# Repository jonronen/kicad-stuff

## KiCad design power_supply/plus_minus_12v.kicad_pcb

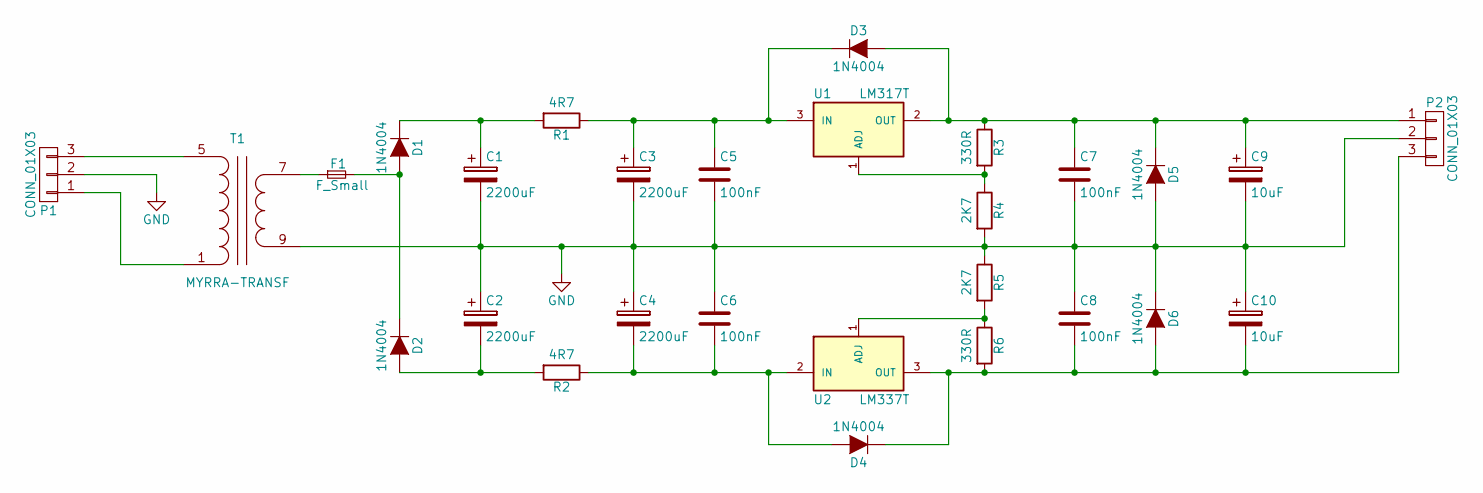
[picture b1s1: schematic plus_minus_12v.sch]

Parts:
C1, C2, C3, C4: 2200uF; C_Radial_D16_L30_P7.5
C5, C6, C7, C8: 100nF; C_Rect_L4_W2.5_P2.5
C9, C10: 10uF; C_Radial_D5_L11_P2
D1, D2, D3, D4, D5, D6: 1N4004; DO-35
F1: F_Small; C_Disc_D6_P5
P1: CONN_01X03; TerminalBlock_Pheonix_MKDS1.5-3pol
P2: CONN_01X03; Socket_MOLEX-KK-RM2-54mm_Lock_3pin_straight
R1, R2: 4R7; Resistor_SMD+THTuniversal_2512_RM10_HandSoldering
R3, R6: 330R; Resistor_SMD+THTuniversal_0805to1206_RM10_HandSoldering
R4, R5: 2K7; Resistor_SMD+THTuniversal_0805to1206_RM10_HandSoldering
T1: MYRRA-TRANSF; Trafo_CHK-EI42-5VA_1xSec
U1: LM317T; TO-220_Neutral123_Vertical
U2: LM337T; TO-220_Neutral123_Vertical

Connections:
GND: C1.2, C2.1, C3.2, C4.1, C5.2, C6.1, C7.2, C8.1, C9.2, C10.1, D5.2 (A), D6.1 (K), P1.2, P2.2, R4.2, R5.1, T1.9 (SA)
unnamed: C1.1, D1.1 (K), R1.2
unnamed: C2.2, D2.2 (A), R2.2
unnamed: C3.1, C5.1, D3.1 (K), R1.1, U1.3 (IN)
unnamed: C4.2, C6.2, D4.2 (A), R2.1, U2.2 (IN)
unnamed: C7.1, C9.1, D3.2 (A), D5.1 (K), P2.1, R3.1, U1.2 (OUT)
unnamed: C8.2, C10.2, D4.1 (K), D6.2 (A), P2.3, R6.2, U2.3 (OUT)
unnamed: D1.2 (A), D2.1 (K), F1.2
unnamed: F1.1, T1.7 (SB)
unnamed: P1.1, T1.1 (AB)
unnamed: P1.3, T1.5 (AA)
unnamed: R3.2, R4.1, U1.1 (ADJ)
unnamed: R5.2, R6.1, U2.1 (ADJ)

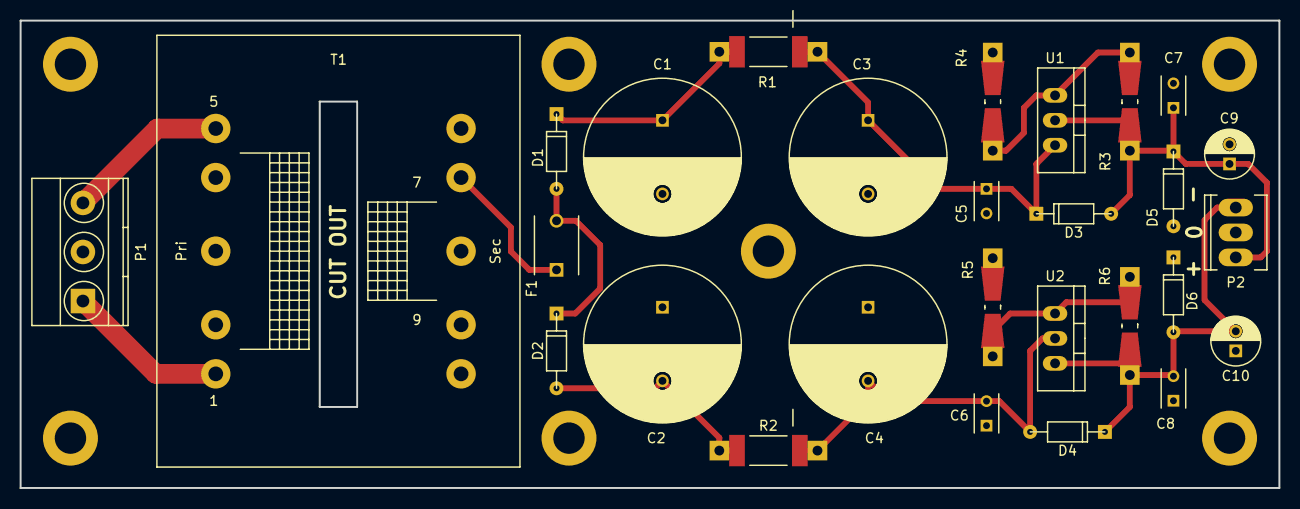
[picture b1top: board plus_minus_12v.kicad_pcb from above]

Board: 2 copper layers, 128.3 x 47.6 mm, 28 parts (0 on the bottom side), 13 nets.

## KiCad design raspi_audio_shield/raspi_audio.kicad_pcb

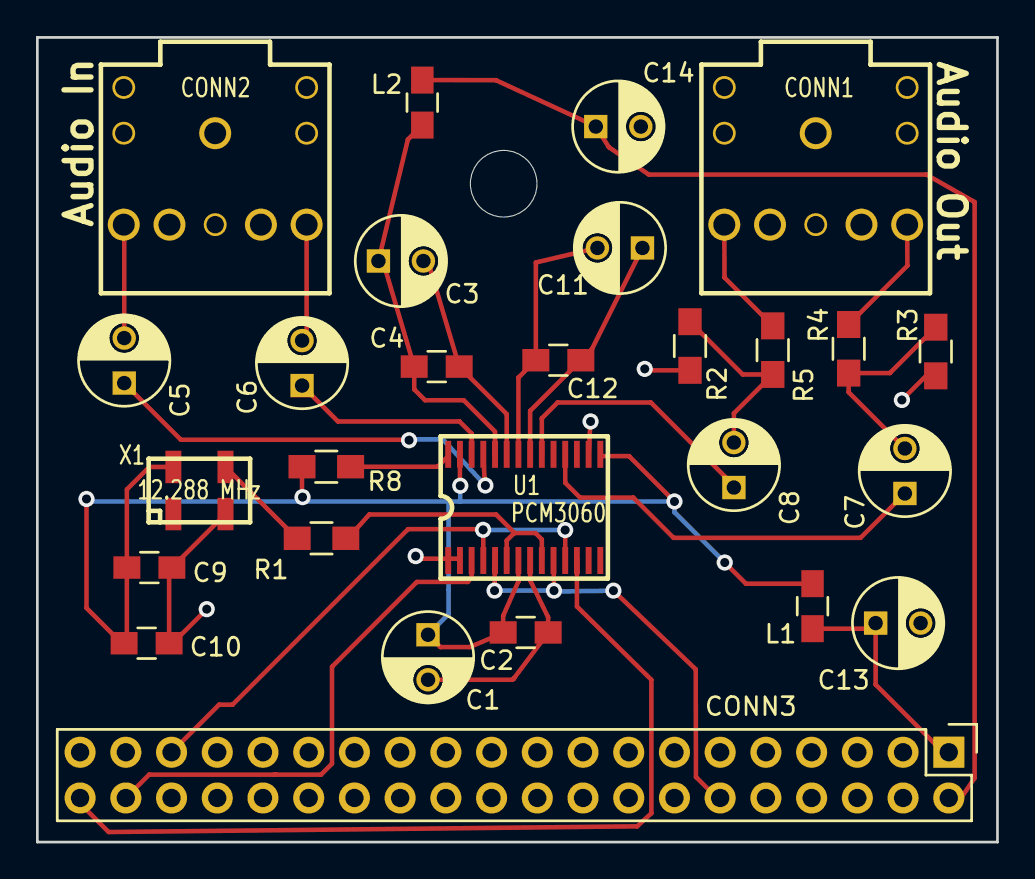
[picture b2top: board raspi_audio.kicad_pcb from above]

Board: 2 copper layers, 53.3 x 44.7 mm, 27 parts (0 on the bottom side), 23 nets.

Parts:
C1, C3, C11: 10uF; C_Radial_D5_L11_P2.5
C2, C4, C10, C12: 100nF; C_0805_HandSoldering
C5, C6: 4.7uF; C_Radial_D5_L11_P2.5
C7, C8: 22uF; C_Radial_D5_L11_P2.5
C9: 10nF; C_0805_HandSoldering
C13, C14: 100uF; C_Radial_D5_L11_P2.5
CONN1, CONN2: JACK_STEREO; AUDIO_STEREO_CONN
CONN3: CONN_02X20; Pin_Header_Straight_2x20
L1, L2: 2200Ohm,200mA; C_0805_HandSoldering
R1: 47R; R_0805_HandSoldering
R2, R3: 10K; R_0805_HandSoldering
R4, R5: 100R; R_0805_HandSoldering
R8: 220K; R_0805_HandSoldering
U1: PCM3060; GEDA_TSSOP28
X1: 12.288 MHz; SMTOSC

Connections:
BCK: CONN3.12, U1.5, U1.10
DATAI: CONN3.40, U1.12
DATAO: CONN3.38, U1.3
Earth: C1.2, C2.2, C3.2, C4.2, C9.2, C10.2, C11.2, C12.2, C13.2, C14.2, CONN1.1, CONN1.4, CONN1.5, CONN2.1, CONN2.4, CONN2.5, CONN3.39, R2.2, R3.1, U1.1, U1.2, U1.8, U1.16, U1.22, U1.23, X1.2
INL: C5.2, CONN2.2
INR: C6.2, CONN2.3
unnamed: C5.1, U1.25
unnamed: C6.1, U1.26
unnamed: C7.1, U1.18
unnamed: C7.2, R3.2, R4.1
unnamed: C8.1, U1.20
unnamed: C8.2, R2.1, R5.2
unnamed: C11.1, C12.1, U1.21
unnamed: C13.1, CONN3.1, L1.2
unnamed: C14.1, CONN3.2, L2.2
unnamed: R1.1, U1.6, U1.9
unnamed: R8.1, U1.28
OUTL: CONN1.2, R5.1
OUTR: CONN1.3, R4.2
SYSCLK: R1.2, X1.3
VCC: C3.1, C4.1, L2.1, U1.24
VDD: C1.1, C2.1, C9.1, C10.1, L1.1, R8.2, U1.7, U1.15, U1.27, X1.4
WS: CONN3.35, U1.4, U1.11

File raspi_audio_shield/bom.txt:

L1, L2: 2x Ferrite bead, 2.2Kohm@100MHz, 200mA, 1ohm, 0805 SMD
X1: 12.288MHz 3.3V oscillator, FXO-HC536R-12.288, 3.2x5mm SMD
U1: Stereo Audio Codec, TI PCM3060PW, TSSOP-28
R1: Resistor, 47ohm, 0805 SMD
R2, R3: 2x Resistor, 10Kohm, 0805 SMD
R4, R5: 2x Resistor, 100ohm, 0805 SMD
R8: Resistor, 220Kohm, 0805 SMD
C1, C3, C11: 3x Radial Electrolytic Capacitor, 10uF, 50V, 5x11mm
C2, C4, C10, C12: 4x Capacitor, 100nF, 50V, 0805 SMD
C5, C6: 2x Radial Electrolytic Capacitor, 4.7uF, 50V, 5x11mm
C7, C8: 2x Radial Electrolytic Capacitor, 22uF, 50V, 5x11mm
C9: Capacitor, 10nF, 50V, 0805 SMD
C13, C14: 2x Radial Electrolytic Capacitor, 100uF, 35V, 6x11mm
CONN1, CONN2: 2x Stereo Enclosed Socket Chassis Jack
    http://www.taydaelectronics.com/hardware/3-5mm-plugs-jacks/3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
CONN3: Stackable Header, 2.54mm, 2x20 Pins (solder with pins facing up)

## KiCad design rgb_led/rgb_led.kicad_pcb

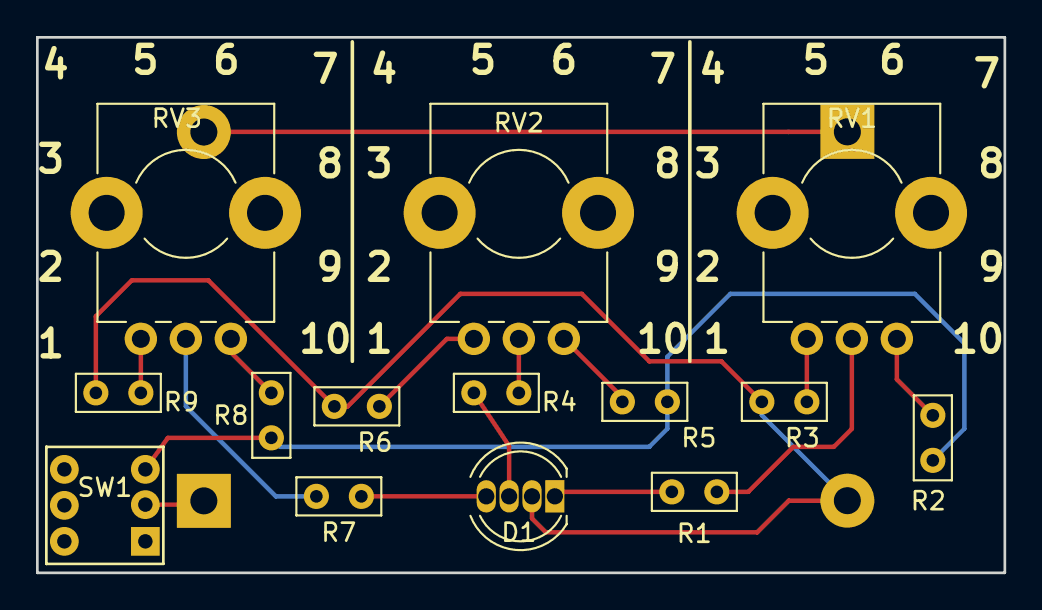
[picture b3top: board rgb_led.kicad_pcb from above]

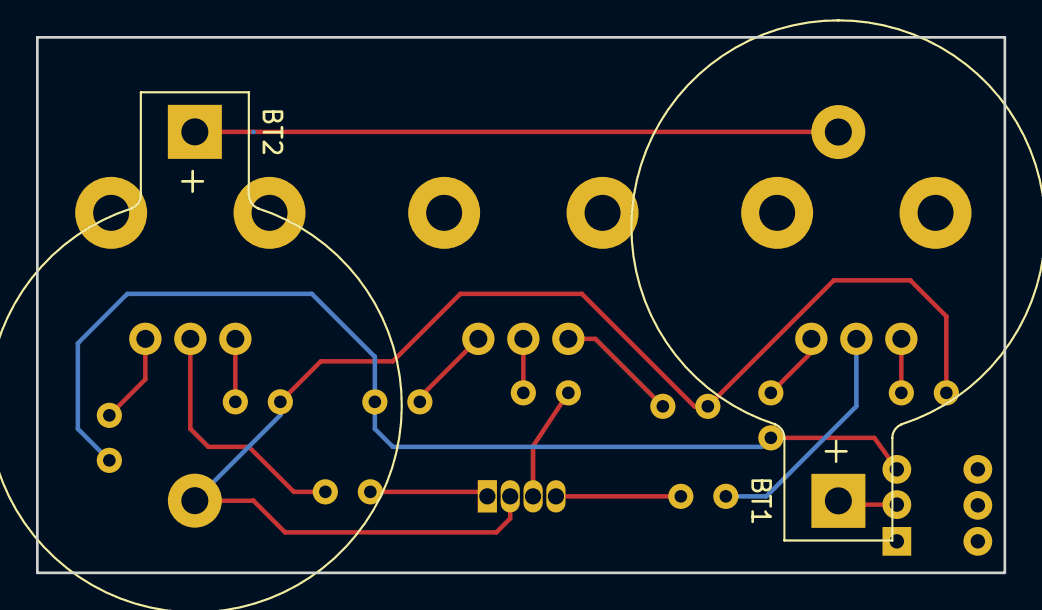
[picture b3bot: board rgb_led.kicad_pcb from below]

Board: 2 copper layers, 53.8 x 29.8 mm, 16 parts (2 on the bottom side), 16 nets.

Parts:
BT1, BT2: Battery_Cell; Keystone_103_1x20mm-CoinCell
D1: LED_RCGB; LED_D5.0mm-4
R1, R2, R3, R4, R5, R6, R7, R8, R9: R; C_Rect_L4.6mm_W2.0mm_P2.50mm_MKS02_FKP02
RV1, RV2, RV3: POT; Potentiometer_Bourns_PTV09A-1_Horizontal
SW1: SW_DPDT_x2; DPDT_6mm

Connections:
unnamed: BT1.1, SW1.2
unnamed: BT1.2, BT2.1
unnamed: BT2.2, D1.2, R3.2, R6.2, R9.2
unnamed: D1.1, R1.2
unnamed: D1.3, R4.2
unnamed: D1.4, R7.2
unnamed: R1.1, RV1.2
unnamed: R2.1, R5.1, R8.1, SW1.3
unnamed: R2.2, RV1.1
unnamed: R3.1, RV1.3
unnamed: R4.1, RV2.2
unnamed: R5.2, RV2.1
unnamed: R6.1, RV2.3
unnamed: R7.1, RV3.2
unnamed: R8.2, RV3.1
unnamed: R9.1, RV3.3

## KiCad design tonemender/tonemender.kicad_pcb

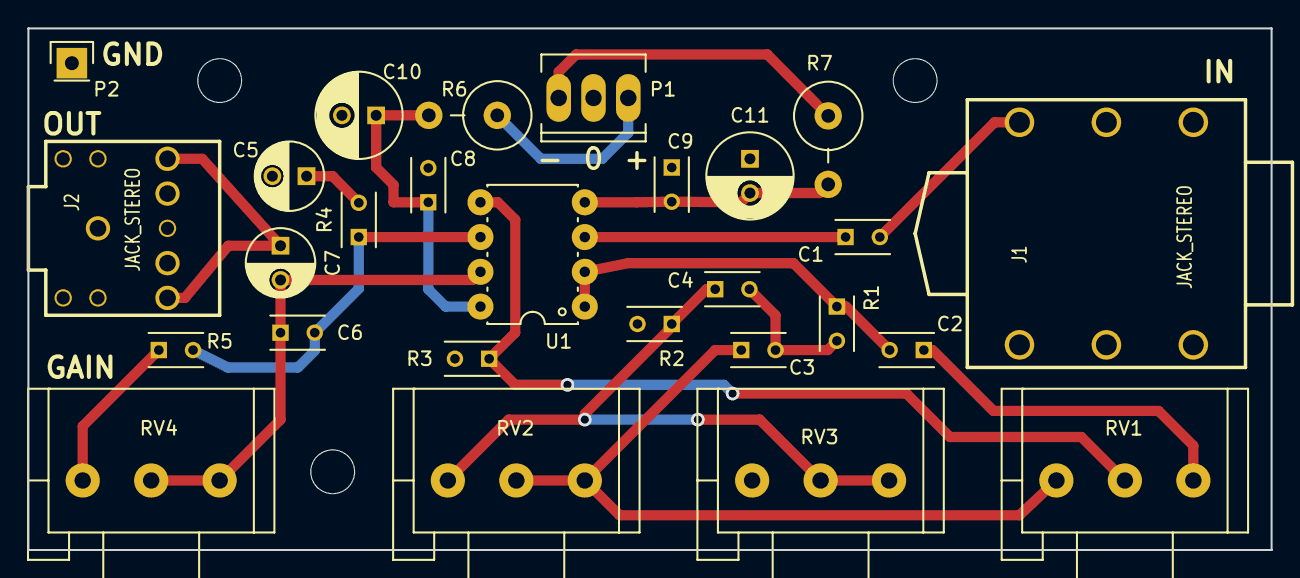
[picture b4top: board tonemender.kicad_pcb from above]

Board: 2 copper layers, 90.8 x 38.1 mm, 27 parts (0 on the bottom side), 18 nets.

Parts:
C1, C3: 470nF; C_Rect_L4_W2.5_P2.5
C2: 470pF; C_Rect_L4_W2.5_P2.5
C4: 220nF; C_Rect_L4_W2.5_P2.5
C5: 47uF; C_Radial_D5_L6_P2.5
C6: 47pF (optional); C_Rect_L4_W2.5_P2.5
C7: 1uF; C_Radial_D5_L6_P2.5
C8, C9: 100nF; C_Rect_L4_W2.5_P2.5
C10, C11: 100uF; C_Radial_D6.3_L11.2_P2.5
J1: JACK_STEREO; audio_635mm_stereo_input
J2: JACK_STEREO; AUDIO_STEREO_CONN
P1: CONN_01X03; Socket_MOLEX-KK-RM2-54mm_Lock_3pin_straight
P2: CONN_01X01; Pin_Header_Straight_1x01
R1: 20K; C_Rect_L4_W2.5_P2.5
R2: 10K; C_Rect_L4_W2.5_P2.5
R3: 1M; C_Rect_L4_W2.5_P2.5
R4: 4.7K; C_Rect_L4_W2.5_P2.5
R5: 620R; C_Rect_L4_W2.5_P2.5
R6, R7: 10R; Resistor_Vertical_RM5mm
RV1, RV2: 50K; Potentiometer_Alps-RK16-single
RV3: 10K; Potentiometer_Alps-RK16-single
RV4: 500K; Potentiometer_Alps-RK16-single
U1: OPA1612; PDIP-8

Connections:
+12V: C8.1, C10.1, R6.2, U1.8
-12V: C9.2, C11.2, R7.2, U1.4
GND: C5.2, C8.2, C9.1, C10.2, C11.1, J1.1, J1.4, J1.5, J2.1, P1.2, P2.1, R2.2, R3.2, RV3.3
unnamed: C1.1, U1.3
unnamed: C1.2, J1.2
unnamed: C2.1, RV1.1
unnamed: C2.2, R1.1, U1.1, U1.2
unnamed: C3.1, RV1.3, RV2.1, RV2.2
unnamed: C3.2, C4.2, R1.2
unnamed: C4.1, R2.1, RV2.3, RV3.1, RV3.2
unnamed: C5.1, R4.2
unnamed: C6.1, C7.2, RV4.1, RV4.2, U1.7
unnamed: C6.2, R4.1, R5.2, U1.6
unnamed: C7.1, J2.2, J2.3
unnamed: P1.1, R6.1
unnamed: P1.3, R7.1
unnamed: R3.1, RV1.2, U1.5
unnamed: R5.1, RV4.3

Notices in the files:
tonemender/tonemender.kicad_pcb:
(C) 2014-2016
